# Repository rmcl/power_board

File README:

PowerBOARD
===============

A simple breakout board with a switching DC/DC power supply (MPM3610A) and a current sensor (INA219). Accepts ~6-21V and outpus 5V.

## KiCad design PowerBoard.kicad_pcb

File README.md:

PowerBOARD v1.3
===============

A simple breakout board with a switching DC/DC power supply (MPM3610A) and a I2C current sensor (INA219). Accepts ~6-21V and outputs 5V 1.2A.

Changelog
-----

v2
* Dropped schottky diode on Vin.
* Added jumpers for A0 & A1

Todo
----
* Make the MPM3610 show up in the 3d model
* Add a header pin for the MPM3610A's enable (en) pin.

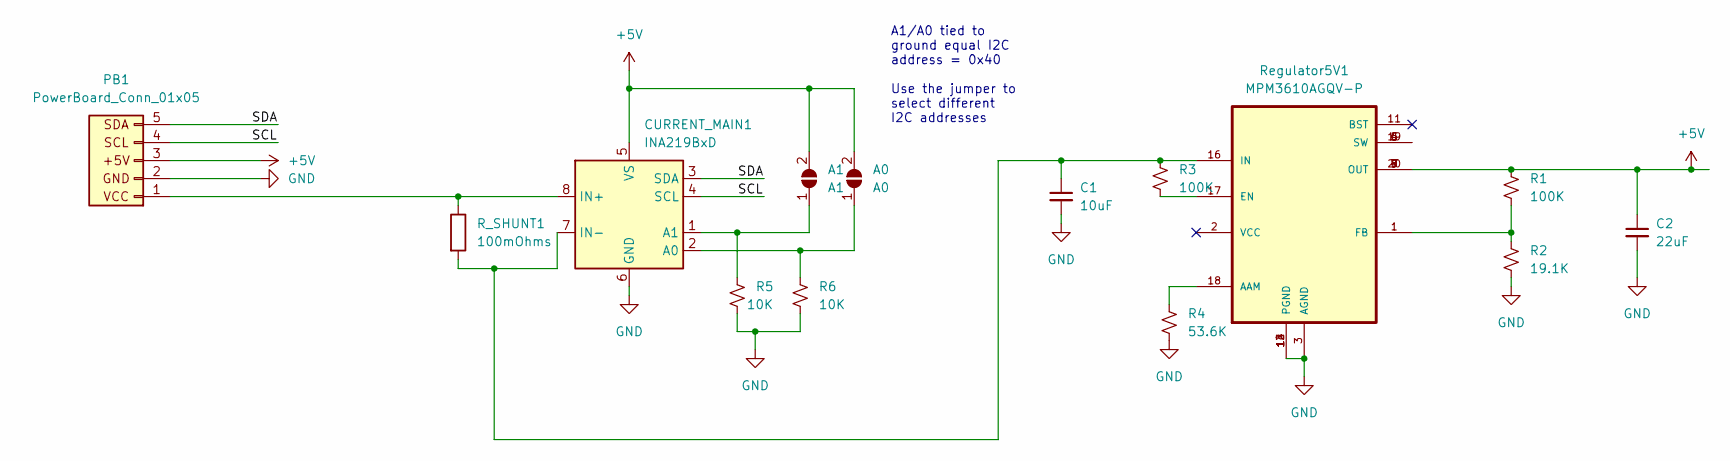
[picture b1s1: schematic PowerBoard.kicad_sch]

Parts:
A0: A0; SolderJumper-2_P1.3mm_Open_Pad1.0x1.5mm
A1: A1; SolderJumper-2_P1.3mm_Open_Pad1.0x1.5mm
C1: 10uF; C_0603_1608Metric_Pad1.08x0.95mm_HandSolder
C2: 22uF; C_0603_1608Metric_Pad1.08x0.95mm_HandSolder
CURRENT_MAIN1: INA219BxD; SOIC-8_3.9x4.9mm_P1.27mm
PB1: PowerBoard_Conn_01x05; PinHeader_1x05_P2.54mm_Vertical
R1, R3: 100K; R_0603_1608Metric
R2: 19.1K; R_0603_1608Metric
R4: 53.6K; R_0603_1608Metric
R5, R6: 10K; R_0603_1608Metric
R_SHUNT1: 100mOhms; R_2512_6332Metric
Regulator5V1: MPM3610AGQV-P; CONV_MPM3620AGQV-P; PARTREV 1.0

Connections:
+5V: A0.2 (B), A1.2 (B), C2.1, CURRENT_MAIN1.5 (VS), PB1.3 (+5V), R1.1, Regulator5V1.7 (OUT), Regulator5V1.8 (OUT), Regulator5V1.9 (OUT), Regulator5V1.20 (OUT)
/SCL: CURRENT_MAIN1.4 (SCL), PB1.4 (SCL)
/SDA: CURRENT_MAIN1.3 (SDA), PB1.5 (SDA)
GND: C1.2, C2.2, CURRENT_MAIN1.6 (GND), PB1.2 (GND), R2.2, R4.2, R5.2, R6.2, Regulator5V1.3 (AGND), Regulator5V1.12 (PGND), Regulator5V1.13 (PGND), Regulator5V1.14 (PGND)
unnamed: A0.1 (A), CURRENT_MAIN1.2 (A0), R6.1
unnamed: A1.1 (A), CURRENT_MAIN1.1 (A1), R5.1
unnamed: C1.1, CURRENT_MAIN1.7 (IN-), R3.1, R_SHUNT1.2, Regulator5V1.16 (IN)
unnamed: CURRENT_MAIN1.8 (IN+), PB1.1 (VCC), R_SHUNT1.1
unnamed: R1.2, R2.1, Regulator5V1.1 (FB)
unnamed: R3.2, Regulator5V1.17 (EN)
unnamed: R4.1, Regulator5V1.18 (AAM)
unnamed: Regulator5V1.4 (SW), Regulator5V1.5 (SW), Regulator5V1.6 (SW), Regulator5V1.19 (SW)

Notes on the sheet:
A1/A0 tied to ground equal I2C address = 0x40 Use the jumper to select different I2C addresses

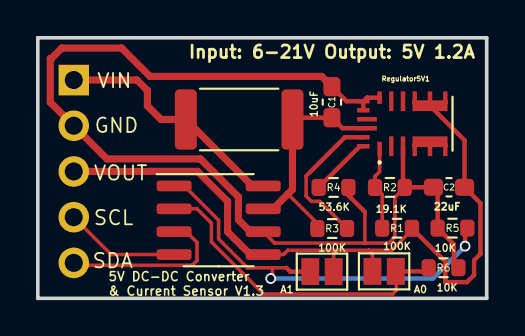
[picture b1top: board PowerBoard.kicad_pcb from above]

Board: 2 copper layers, 24.9 x 14.5 mm, 14 parts (1 on the bottom side), 12 nets.

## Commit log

2022-11-27 initial commit.
2022-11-27 update readme.
2022-11-27 added 3d model.
2022-11-27 add text.
2022-11-27 added bill of material.
2022-12-11 add additional AAM resistor and increment board version. Instructions for 3.3V output rather than 5V if desired.
2022-12-13 version 1.2.
2022-12-13 fix typo.
2022-12-13 update todo.
2022-12-23 update to 1.3.
2022-12-23 bump version in readme.
